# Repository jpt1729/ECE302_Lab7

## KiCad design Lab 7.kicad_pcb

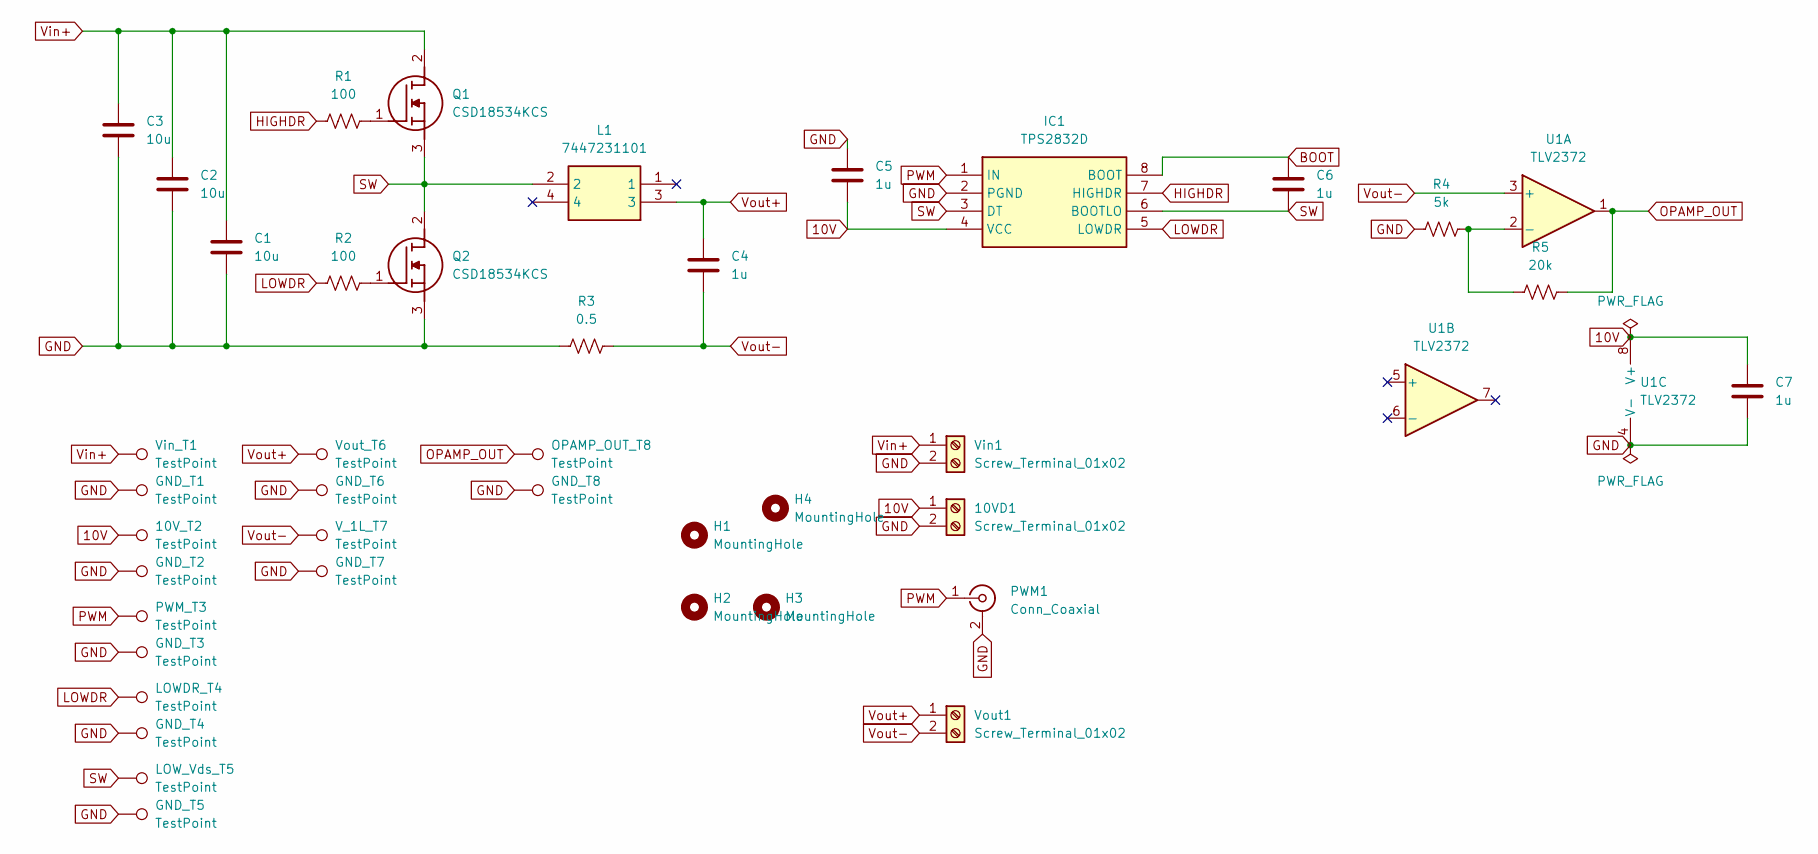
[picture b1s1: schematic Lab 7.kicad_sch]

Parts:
10VD1: Screw_Terminal_01x02; PhoenixContact_MSTBA_2,5_2-G_1x02_P5.00mm_Horizontal
10V_T2: TestPoint; TestPoint_Keystone_5010-5014_Multipurpose
C1, C2, C3: 10u; C_Disc_D3.8mm_W2.6mm_P2.50mm
C4, C5, C6, C7: 1u; C_Disc_D3.8mm_W2.6mm_P2.50mm
GND_T1, GND_T2, GND_T3, GND_T4, GND_T5, GND_T6, GND_T7, GND_T8: TestPoint; TestPoint_Keystone_5010-5014_Multipurpose
H1, H2, H3, H4: MountingHole; MountingHole_3.2mm_M3
IC1: TPS2832D; SO-8_3.9x4.9mm_P1.27mm; Manufacturer_Part_Number TPS2832D; Mouser Part Number 595-TPS2832D
L1: 7447231101; Manufacturer_Part_Number 7447231101
LOWDR_T4: TestPoint; TestPoint_Keystone_5010-5014_Multipurpose
LOW_Vds_T5: TestPoint; TestPoint_Keystone_5010-5014_Multipurpose
OPAMP_OUT_T8: TestPoint; TestPoint_Keystone_5010-5014_Multipurpose
PWM1: Conn_Coaxial; BNC_Amphenol_B6252HB-NPP3G-50_Horizontal
PWM_T3: TestPoint; TestPoint_Keystone_5010-5014_Multipurpose
Q1, Q2: CSD18534KCS; TO-220-3_Vertical; Manufacturer_Part_Number CSD18534KCS; Mouser Part Number 595-CSD18534KCS
R1, R2: 100; R_Axial_DIN0207_L6.3mm_D2.5mm_P10.16mm_Horizontal
R3: 0.5; R_Axial_DIN0922_L20.0mm_D9.0mm_P30.48mm_Horizontal
R4: 5k; R_Axial_DIN0207_L6.3mm_D2.5mm_P10.16mm_Horizontal
R5: 20k; R_Axial_DIN0207_L6.3mm_D2.5mm_P10.16mm_Horizontal
U1: TLV2372; SO-8_3.9x4.9mm_P1.27mm
V_1L_T7: TestPoint; TestPoint_Keystone_5010-5014_Multipurpose
Vin1: Screw_Terminal_01x02; PhoenixContact_MSTBA_2,5_2-G_1x02_P5.00mm_Horizontal
Vin_T1: TestPoint; TestPoint_Keystone_5010-5014_Multipurpose
Vout1: Screw_Terminal_01x02; PhoenixContact_MSTBA_2,5_2-G_1x02_P5.00mm_Horizontal
Vout_T6: TestPoint; TestPoint_Keystone_5010-5014_Multipurpose

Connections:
10V: 10VD1.1, 10V_T2.1, C5.2, C7.1, IC1.4 (VCC), U1.8 (V+)
BOOT: C6.1, IC1.8 (BOOT)
GND: 10VD1.2, C1.2, C2.2, C3.2, C5.1, C7.2, GND_T1.1, GND_T2.1, GND_T3.1, GND_T4.1, GND_T5.1, GND_T6.1, GND_T7.1, GND_T8.1, IC1.2 (PGND), PWM1.2 (Ext), Q2.3 (S), R3.2, R4.1, U1.4 (V-), Vin1.2
HIGHDR: IC1.7 (HIGHDR), R1.1
LOWDR: IC1.5 (LOWDR), LOWDR_T4.1, R2.2
unnamed: Q1.1 (G), R1.2
unnamed: Q2.1 (G), R2.1
unnamed: R4.2, R5.1, U1.2 (-)
OPAMP_OUT: OPAMP_OUT_T8.1, R5.2, U1.1
PWM: IC1.1 (IN), PWM1.1 (In), PWM_T3.1
SW: C6.2, IC1.3 (DT), IC1.6 (BOOTLO), L1.2, LOW_Vds_T5.1, Q1.3 (S), Q2.2 (D)
Vin+: C1.1, C2.1, C3.1, Q1.2 (D), Vin1.1, Vin_T1.1
Vout+: C4.1, L1.3, Vout1.1, Vout_T6.1
Vout-: C4.2, R3.1, U1.3 (+), V_1L_T7.1, Vout1.2

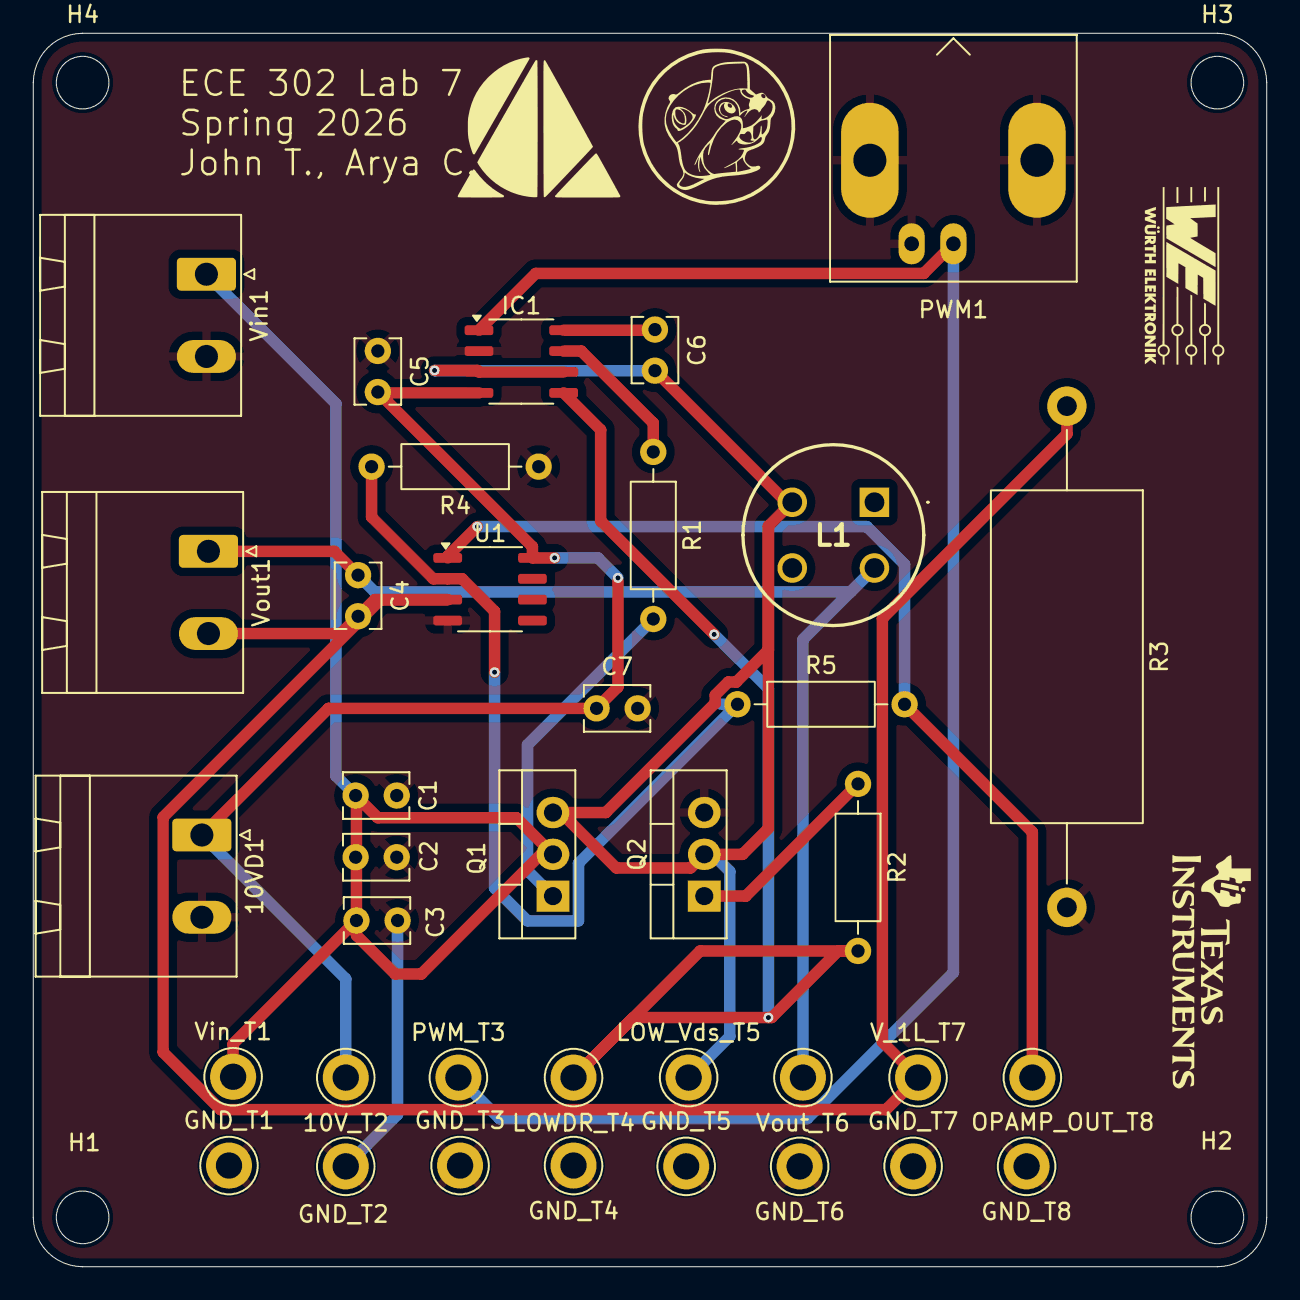
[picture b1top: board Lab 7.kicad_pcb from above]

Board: 2 copper layers, 75.0 x 75.0 mm, 41 parts (0 on the bottom side), 14 nets.

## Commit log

2026-03-02 schematic done
2026-03-06 stuff
2026-03-06 connecting ground
